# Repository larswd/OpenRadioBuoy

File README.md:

# The Open Radio Buoy (ORB)
This repository contains the firmware, list of hardware and PCB schematics that collectively make up the Open Radio Buoy (ORB), as described in our paper which you can read [here](https://arxiv.org/abs/2601.05615). The buoy is designed to be a low-cost, open-source drifter for coastal water measurements. The archive is currently incomplete, but more updates will come. 

## List of hardware components

### Drifter

A single ORB drifter's electronics is made up of the following components, with links to manufacturer website. 

| Quantity | Component | Note |
| -------- | --------- | ---- |
| 1 | [Seeed Studio Wio-E5 mini](https://wiki.seeedstudio.com/LoRa_E5_mini/) | Comes with actory protection which needs to be disabled manually |
| 1 | [Adafruit Ultimate GPS](https://www.adafruit.com/product/746)          | Comes with a holder for a CR1220 clock battery to remember last fix.| 
| 1 | [Adafruit SD Breakout](https://www.adafruit.com/product/254)           | | 
| 1 | [DS18B20 temperature sensor](https://www.sparkfun.com/temperature-sensor-waterproof-ds18b20.html) | |
| 1 | [Pololu 3.3 V Step up/Step down voltage regulator](https://www.pololu.com/product/2122) | |
| 1 | 10 kOhm resistor  |
| 1 | 4.7 kOhm resistor  |
| 2 | 33.0 Ohm resistors |
| 1 | Magnetic switch         | Normally open is *strongly* recommended. Not mandatory. |
| 1 | [CAB-14574 connector](https://no.mouser.com/ProductDetail/474-CAB-14574) | Not mandatory, but makes arming and disarming the drifter easier |
| 1 | Strong magnet | To turn off the buoy from outside the buoy container | Not mandatory |

As for battery power, the buoy works with any kind of power source with a voltage between 2.7 and 11.8 V, as per the Pololu documentation. This can be either a Lithium battery such as [Saft LSH20](https://www.nkon.nl/novat/saft-lsh-20-lithium-battery-3-6v.html), although any user should be aware of the [risks of using Lithium powered batteries](https://www.relionbattery.com/blog/the-truth-about-lithium-batteries-and-safety). Alternatively, several alkaline batteries (as was done by the [SFY](https://github.com/gauteh/sfy)) in series can be utilised without need of modifying the circuit. 

### Base station

A single ORB base station electronics is made up of the following components, with links to manufacturer website. 

| Quantity | Component | Note |
| -------- | --------- | ---- |
| 1 | [Seeed Studio Wio-E5 mini](https://wiki.seeedstudio.com/LoRa_E5_mini/) | Comes with actory protection which needs to be disabled manually |
| 1 | [Adafruit SD Breakout](https://www.adafruit.com/product/254)           | Not mandatory |
| 1 | [Pololu 5 V Step up/Step down voltage regulator](https://www.pololu.com/product/4082) | |
| 1 | [CAB-14574 connector](https://no.mouser.com/ProductDetail/474-CAB-14574) | Not mandatory, but makes arming and disarming the drifter easier |
| 1 | [Blues Notecard Cellular](https://shop.blues.com/collections/notecard/products/notecard-cellular?variant=44541263118577) | Check the coverage diagram for your area before ordering |
| 1 | [Blues Notecarrier A](https://shop.blues.com/products/carr-al) | |
| 1-2 | Capacitor (One [1F](https://no.mouser.com/ProductDetail/Eaton-Electronics/KVR-5R0V105-R?qs=4ASt3YYao0XQhknEZPCgzw%3D%3D) or two [10F](https://no.mouser.com/ProductDetail/Knowles-Illinois-Capacitor/DGH106Q2R7C?qs=vmHwEFxEFR9tIw5tsmf9eg%3D%3D)) | Capacitor strength dependent on power source |

If you choose to power the base station with Lithium batteries like the aforementioned LSH20, then a single 1 F capacitor is sufficient to keep the base station operational. If, however, you use alkaline batteries as your power source then 10 F capacitors are required to ensure that the high energy spikes drawn by the GSM module can be met. 

### Other components
To code the WiO E5 mini, remember to order at least one [ST link](https://www.adafruit.com/product/2548) and some [Female-Male jumper cables](https://no.rs-online.com/web/p/breadboard-jumper-wires/2048242) in order to be able to upload the software to the buoys and base stations. 

## Assembly instructions

### Electronics assembly - Buoys
Order the [PCBs](https://github.com/larswd/OpenRadioBuoy/tree/main/hardware/buoy_PCB) by uploading the Gerber files folder to your favourite PCB manufacturer, such as [JLCPCB](https://cart.jlcpcb.com/quote?spm=jlcpcb.Public.2006) or [Seeed studio](https://www.seeedstudio.com/fusion_pcb.html). Then order the components listed above according to how many buoys you plan to make. They can be ordered either from the manufacturer, and in many cases from a local electronics distributor. 

The assembly can begin once you have all the components at hand. The PCBs offered are currently Through-Hole PCBs, and requires therefore manual soldering. As both sides of the PCB is utilized in somewhat overlapping segments, it is vital that some components are soldered before others. I would recommend soldering in this order: 

1. Wires to the power pins at the bottom of the PCB
2. Pololu
3. Trim the pins on the back of the Pololu, then tape. 
4. SD card writer
5. Trim the pins on the back of the SD card writer, then tape.
6. GPS
7. Trim GPS pins
8. Wio E5 mini
9. MF pin sockets for the programmable pins
10. DS18B20
11. Resistors
12. Magnetic switch
13. Battery connectors
    
### Electronics assembly - Base stations
Order the [PCBs](https://github.com/larswd/OpenRadioBuoy/tree/main/hardware/BST_PCB) by uploading the Gerber files folder to your favourite PCB manufacturer, such as [JLCPCB](https://cart.jlcpcb.com/quote?spm=jlcpcb.Public.2006) or [Seeed studio](https://www.seeedstudio.com/fusion_pcb.html). Then order components according to the amount of base stations you plan on creating. 
The assembly can begin once you have all the components at hand. The PCBs offered are currently Through-Hole PCBs, and requires therefore manual soldering. Unlike the buoy PCBs, there is little overlap between components and they can be soldered on in pretty much any order. Some things to keep in mind

1. The power regulator will somewhat block easy access to the USB port on the LoRa module. Hence, it is strongly recommended to not solder the module directly onto the board. Instead, we recommend soldering on a 1x5 2.54 mm MF pin header, as the power regulator then easily can be removed and reattached if you need to upload software updates. 
2. Super capacitors have a polarity, indicated by the arrows on both the PCB and often on the capacitors themselves. Please check the data sheet of your capacitor before soldering. 
3. The Notecard might need to be initialized before use. A handy guide can be found [here](https://dev.blues.io/quickstart/notecard-quickstart/notecard-and-notecarrier-a/).
4. The notecard sends the data to Blues' Notehub, which is project based. By default, the ORB base station is set to send the data to a notehub project owned by us. We are willing to share any data we receive as well as the url to our dashboard, but if you want to administrate your data yourself, and who gets access to it, then you can create your own project at [https://notehub.io/projects], then you simply exchange the notehub project url at (currently) line 14 in [the GSM module header](https://github.com/larswd/OpenRadioBuoy/tree/main/firmware/common_libraries/gsm/src/gsm.h) with your new project url (which should look something like ```me.proton.larswd:my_cool_project```)

### Installation instructions - Buoy
The installation of the ORB firmware is a two-step process. First, you need to remove the write protection that the WiO-E5-mini comes with out of the box. To do so, you first need a USB C cable and a [ST-Link](https://www.adafruit.com/product/2548). Then, download the [STM32CubeProgrammer](https://www.st.com/en/development-tools/stm32cubeprog.html#get-software), and install it. Once it is installed, connect the Wio-E5 mini to your laptop via both the USB C cable and with the ST-link. Here, you need to connect the right pins, and we list them as (ST Link pin/Wio pin), 
- (RST/RST),
- (SWCLK/CLK),
- (SWDIO/DIO),
- (GND/GND).
Afterwards, set ```shared``` to ```Enabled``` and ```Reset mode``` to ```Hardware reset```. If you press the circular arrows button, then if everything works you should see under the **OB** header an option called **Read out protection**, set this drop-down menu to AA and press **Apply**. The buoy is now programmable! See a helpful visual guide below: 

The next step is to upload the firmware. If you are happy with the default configuration, then you can jump to the next paragraph. Otherwise, you can configure most important parameters in the [configuration file](firmware/drifter/src/config.h). What each parameter does is described in the [drifter README file](firmware/drifter/README.md).

Once you have a configuration file you are satisfied with, you can upload the firmware to the buoy. To do so, we use [PlatformIO IDE for vscode](https://docs.platformio.org/en/latest/integration/ide/vscode.html), an extension for visual studio code made for programming microcontrollers. Once you have installed platformIO, click **Open project** under the **PIO Home** tab, and navigate to the *firmware/drifter* folder and click **Open drifter**. From here, platformio will open and read the necessary configurations. Once the project has finished loading, which you can see when several new buttons have appeared at the bottom taskbar in visual studio code, then you can upload the code. An image of a fully loaded platformio instance is shown below, in particular note the checkmark and arrow key at the very bottom. 

To upload the code, connect the ORB to your computer both with the ST link (connection instructions are given above) and the USB C cable, then press the upload button (The arrow icon), then wait until the terminal that popped up states something close to 
```
============================================= [SUCCESS] Took 3.12 seconds =============================================
```
### Installation instructions - Base station
The steps for installing the firmware to the base station is more or less the same as the buoy one, with the exception that you instead open the **basestation** project rather than the **drifter** project. Furthermore, you should here remember to go into the ```config.h``` file and set a unique base station ID. See the line where it says:
static constexpr uint8_t base_station_ID            {x};```
Where ```x``` is some number. Set ```x``` to any whole number between 0 and 255 that you have not previously used in your base station fleet, then upload the code to the base station. **REMEMBER**: See bullet point 4 of the assembly instructions for the base station regarding data management. 

### Final assembly 

The container components we used are given in the table below 

| Component | Role |
| --------- | ---- |
| [Pipe connector](https://www.biltema.no/bygg/vvs/sanitet-og-vann/avlop/innendors-avlop-gra/innendors-avlop-gra-75-mm/avlopsror-skjotemuffe-75-mm-2000059003) | Main electrical component housing |
| [Lid 75 mm](https://www.biltema.no/bygg/vvs/sanitet-og-vann/avlop/innendors-avlop-gra/innendors-avlop-gra-75-mm/avlopsror-endestopp-75-mm-2000059011) | Top lid |
| [Reduction 75->50mm](https://www.biltema.no/bygg/vvs/sanitet-og-vann/avlop/innendors-avlop-gra/innendors-avlop-gra-75-mm/avlopsror-reduksjon-o-7550-mm-2000065100) | Ballast and battery container |
|[Lid 50 mm](https://www.biltema.no/bygg/vvs/sanitet-og-vann/avlop/innendors-avlop-gra/innendors-avlop-gra-50-mm/avlopsror-endestopp-o-50-mm-2000065102) | Bottom lid |
| [Large cable gland](https://no.rs-online.com/web/p/cable-glands/6694673) | Cable gland for the antenna |
| [Small cable gland](https://no.rs-online.com/web/p/cable-glands/6694660) | Cable gland for DS18B20 |
| [Ballast](https://www.frederiksen-scientific.no/produkt/lodd-med-krok-200-g/191002) | We use 300 grams of tin ballast in each ORB drifter |
| [XPS 300](https://thaugland.no/butikk/byggevarer/isolasjon/mark-grunn-isolasjon/xps/jackon-isolasjon-xps-20mm-300-jackofoam/) | 20 mm isolation foam as a flotation device around the top for increased stability. |

To assemble, drill two holes in the top lid for the two cable glands. Thereafter, sand the lid to ensure that the top is as uniform as possible. Apply generously with grease on each of the rubber bands on the cable glands and inside the pipes. Insert the fully assembled ORB electronics through the cable glands in the lid. Tighten the antenna gland, but not the thermistor gland, and watch carefully to ensure that the tightening does not loosen the antenna connection to the main circuit board. Insert the bottom lid into the reduction, then place the ballast in the bottom 50 mm diameter pipe, use silicone or other lipophile glue to ensure that it stays put, and add a small cardboard or plastic disc at the top to ensure an even surface. Mark where the magnetic switch is supposed to be placed on the pipe connector with permanent marker, then tape the switch on the other side underneath the marker. Be careful, as improper switch placement means that it is difficult to check if the buoy is turned off while inactive. Cut out a small square or disk of the XPS 300, approximately 15 cm wide at the widest, and cut a 75 mm diameter hole in the middle. Insert the lid into the XPS 300, and then into the pipe connector. Connect the battery to the electronics, and validate that the switch works as intended. Finally, insert the reduction into the connector, and seal the buoy by tightening the thermistor cable gland. 

Your ORB drifter is now ready to use. 

### Final assembly - Base station

As the base stations will, most likely, not be floating in water directly, there is significantly more leeway in container design. Pick any waterproof container large enough, and drill a single hole large enough for the [cable gland](https://no.rs-online.com/web/p/cable-glands/6694673). In our deployments, we used this [fishing box](https://www.clasohlson.com/no/Vanntett-boks-/p/31-8544) which could fit three D Cell batteries and the base station, although it was a bit too cramped. Hence, we recommend finding a slightly larger container if possible. 

## Images and deployments
Images from the deployments will come soon. 

## A small thanks 
We would also like to thank the authors of the many open source libraries that collectively form the code base of the Open Radio Buoy. In no particular order, we wish to express our gratitude to 
- [Paul Stoffregen and contributors' OneWire](https://github.com/PaulStoffregen/OneWire)
- [Mikal Hart and contributors' TinyGPSplus](https://github.com/mikalhart/TinyGPSPlus)
- [Jan Gromeš and contributors's Radiolib](https://github.com/jgromes/RadioLib)
- [Bill Greiman's SdFat](https://github.com/greiman/SdFat)
- [Jean Rabault's OpenMetBuoy](https://github.com/jerabaul29/OpenMetBuoy-v2021a)

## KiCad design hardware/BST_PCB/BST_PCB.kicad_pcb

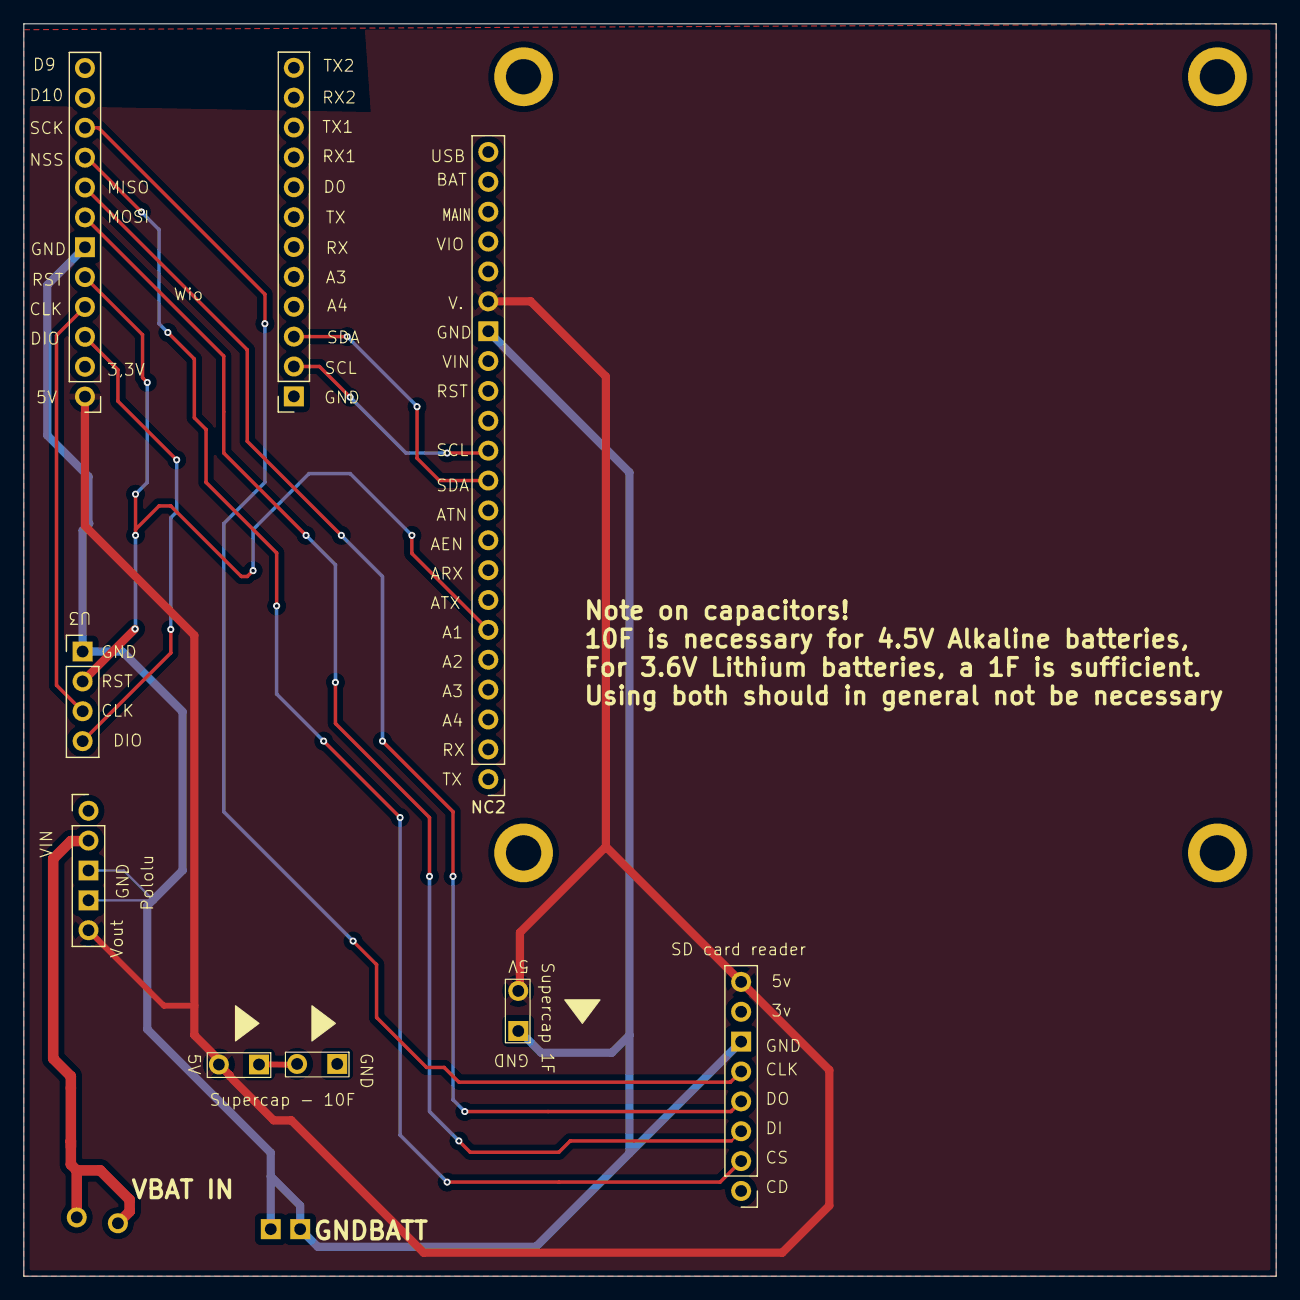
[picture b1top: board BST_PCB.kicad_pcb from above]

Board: 2 copper layers, 106.5 x 106.5 mm, 8 parts (0 on the bottom side), 11 nets.

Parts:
NC2: notecard
Pololu: Pololu5v
SD card reader: SDReader
Supercap2: Supercap
Supercap 1F: Supercap
Supercap - 10F: Supercap
U3: STLINK
Wio: Wio E5 mini

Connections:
5v: NC2.5v, Pololu.Vout (Vin), SD card reader.5v, Supercap2.5V (5v), Supercap 1F.5V (5v), Wio.5V
GND: NC2.Gn (GND), Pololu.GND, Pololu.Gn (GND), SD card reader.Gn (GND), Supercap 1F.vout (GND), Supercap - 10F.vout (GND), U3.Gn (GND), Wio.Gn (GND)
unnamed: NC2.13n (AUX1), U3.RST, Wio.RST
unnamed: NC2.7n (SCL), Wio.D8 (SCL)
unnamed: NC2.8n (SDA), Wio.A0 (SDA)
unnamed: U3.CLK, Wio.CLK
unnamed: U3.DIO, Wio.A7 (DIO)
unnamed: SD card reader.DO, Wio.A6 (CLK)
unnamed: SD card reader.DI, Wio.A5 (MOSI)
unnamed: SD card reader.CS, Wio.NSS
unnamed: SD card reader.CLK, Wio.A1 (SCK)

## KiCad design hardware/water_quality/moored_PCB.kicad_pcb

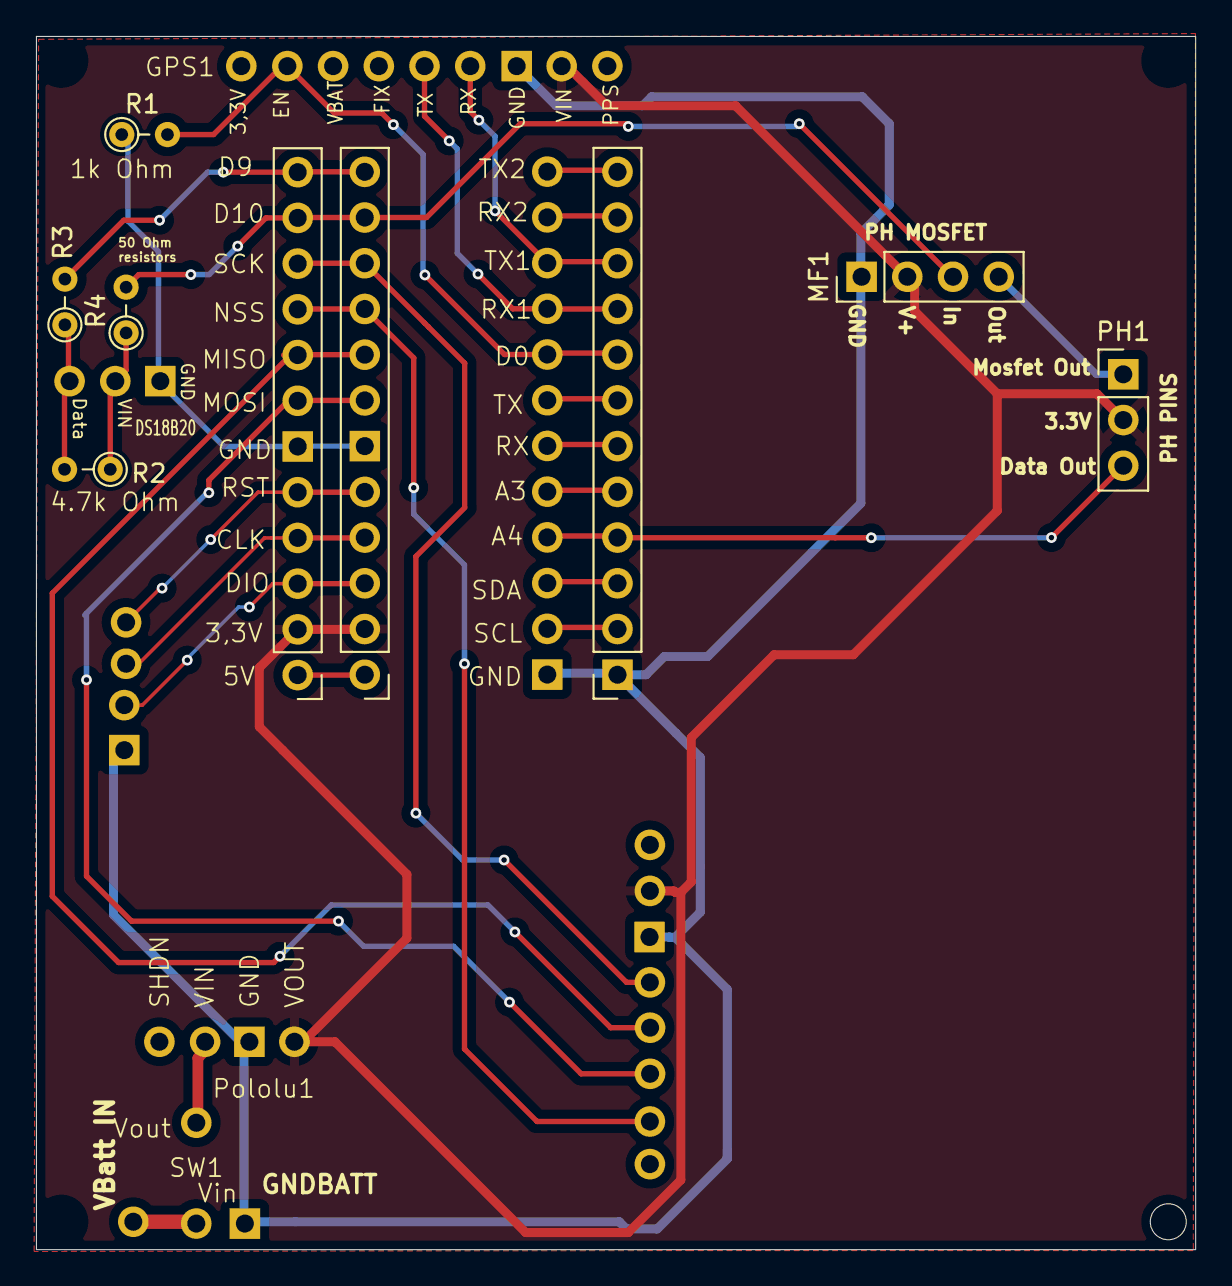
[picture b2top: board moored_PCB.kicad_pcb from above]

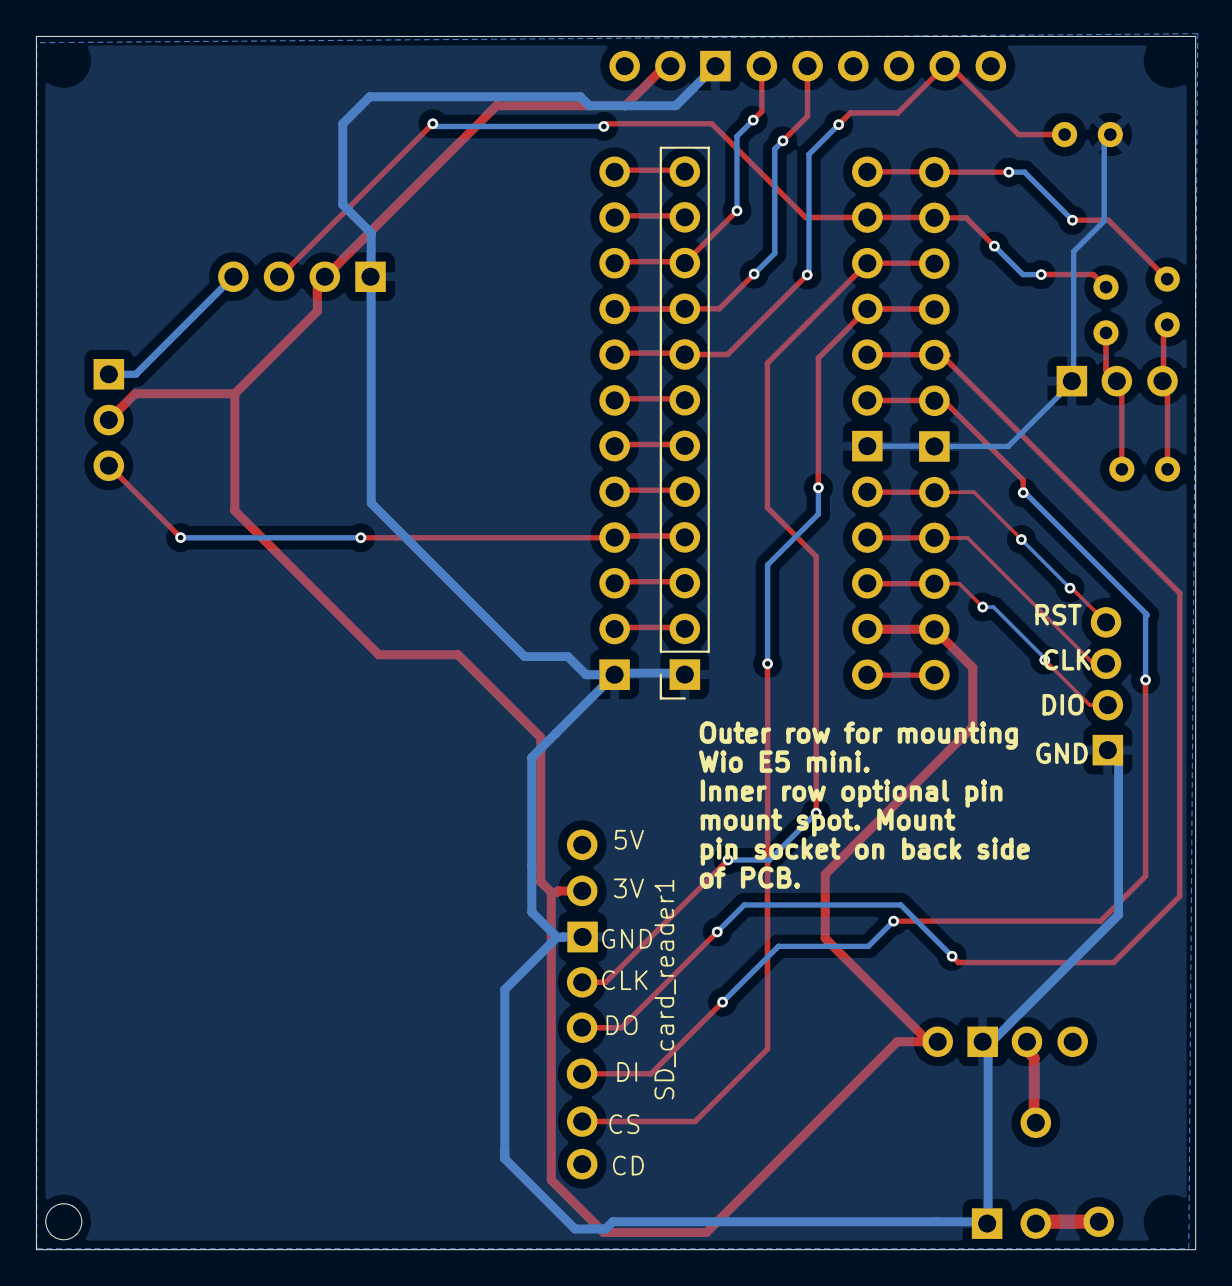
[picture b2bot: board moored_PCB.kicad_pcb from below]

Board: 2 copper layers, 64.4 x 67.4 mm, 13 parts (2 on the bottom side), 14 nets.

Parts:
DS18B20: DS18B20
GPS1: GPS
MF1: PinHeader_1x04_P2.54mm_Vertical
PH1: PinHeader_1x03_P2.54mm_Vertical
Pololu1: Pololu3,3V
R1: 1k Ohm; R_Axial_DIN0204_L3.6mm_D1.6mm_P2.54mm_Vertical
R2: 4.7k Ohm; R_Axial_DIN0204_L3.6mm_D1.6mm_P2.54mm_Vertical
R3, R4: 50 Ohm; R_Axial_DIN0204_L3.6mm_D1.6mm_P2.54mm_Vertical
RHS Wio pins: PinSocket_1x12_P2.54mm_Vertical
SD_card_reader1: 254; SD_writer
SW1: SW_Reed; ReedSwitch
Wio1: WIO_E5_THT

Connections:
3V: GPS1.3V (VIN), MF1.2, PH1.2, Pololu1.3V (Vout), SD_card_reader1.3V, Wio1.3V (3,3V)
GND: DS18B20.Gn (GND), GPS1.Gn (GND), MF1.1, Pololu1.Gn (GND), R1.1, RHS Wio pins.1, SD_card_reader1.Gn (GND), Wio1.Gn (GND)
MISO: SD_card_reader1.SDDO (DO), Wio1.A6 (MISO)
MOSI: SD_card_reader1.SDDI (DI), Wio1.A5 (MOSI)
NSS: SD_card_reader1.SDCS (CS), Wio1.NSS
unnamed: DS18B20.TD (D), R2.2, R3.1
unnamed: DS18B20.TV (Vin), R2.1, R4.1
unnamed: GPS1.2G (EN), R1.2, RHS Wio pins.8, Wio1.D0
unnamed: GPS1.6G (RX), RHS Wio pins.10, Wio1.TX1
unnamed: GPS1.5G (TX), RHS Wio pins.9, Wio1.RX1
unnamed: Pololu1.Pin (Vin), SW1.1
unnamed: R3.2, Wio1.D9
unnamed: MF1.3, R4.2, Wio1.D10
SCK: SD_card_reader1.SDCL (CLK), Wio1.A1 (SCK)

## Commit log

2025-12-19 Update README with project details and structure
    Added project title, description, and sections for installation, hardware, and images.
2025-12-19 Buoy PCB added
2025-12-19 BST PCB
2025-12-19 Added GPS example
2026-02-10 Buoy code ready
2026-02-20 Base station firmware added, migration to shared libraries begun
2026-02-20 BST now uses shared SD library
2026-02-20 Some documentation added, GSM library moved to common libraries
2026-02-23 All libraries moved to separate folder. Both BST and drifter compiles
2026-02-25 Removed clutter
2026-02-27 More documentation
2026-03-17 read GPS example fixed, removed redundant dependency. Added in OneWire by Paul Stofregen to the Thermo manager for compatability
2026-03-17 Add thanks section for open source contributors
    Added a gratitude section to acknowledge open source library authors.
2026-03-17 Added thermometre rading example.
2026-03-17 Added credit to OMB
2026-03-17 Enhance thermo_manager library description
    Updated the description of the thermo_manager library to include compatibility information with the OpenMetBuoy thermistor library.
2026-03-17 Enhance README with common modules information
    Added a section for common modules with descriptions and dependencies in the README.
2026-03-17 Cleanup, removed unused config params
2026-03-17 Correcting parameter
2026-03-17 Enhance README with configuration parameters
    Added a comprehensive configuration file parameter list to the README.
2026-03-17 More cleanup
2026-04-20 Simpler message creation
2026-04-20 Import of extra libraries, parent dir only
2026-04-20 Platformio basestation include lib
2026-04-20 More explicit LoRa send frequency
2026-04-20 Handshake. Fix in setup and loop
2026-04-20 BaseStationID
2026-04-20 Removed uneccessary comment
2026-06-10 Pinned RadioLib to 7.6.0 due to build error
2026-06-10 Making strings equal to save space
2026-06-10 Extra debug prints
2026-06-10 Simpler message extraction. Minor refactoring.
2026-06-10 Bugfix sleep time
2026-06-10 More robust communication with send delay after handshake. New function ConnectToBasestation.
2026-06-10 Split loop method
2026-06-10 Basestation: reduced sd writes before receiving messages for more robust communication. Also fixed radiolib for basestation.
2026-06-10 Removed unecessary debug print
2026-06-10 Added debugprint
2026-06-16 Merging into pull request
2026-06-22 Change resistor value in README
    Updated resistor specification from 1.0 kOhm to 10 kOhm.
2026-06-22 Fixed schematic bugs
2026-06-22 Added more documentation, fixed BST PCB
2026-06-25 Fix battery holder type and typos in README
    Corrected battery holder type for Adafruit Ultimate GPS and fixed minor typos throughout the document.
